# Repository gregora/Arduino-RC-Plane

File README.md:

# Arduino-RC-Plane
An RC airplane, controlled by a custom flight controller based on Arduino Nano.

## CAD

CAD files are available on OnShape [here](https://cad.onshape.com/documents/968e81f1afc8243e275bf7ca/w/acaf7929af669ea720083764/e/5f49399fe13c6903e510c987?renderMode=0&uiState=66e208f6a35c2d67603a374c)

## Controller hardware

The following devices are necessary to recreate the flight controller:
* Arduino Nano microcontroller
* BNO055 Adafruit absolute orientation sensor
* CC1101 radio module

* Flysky radio receiver (or any receiver with iBus)

## Flight modes

The controller enables you to choose from a few different modes of flying. A mode of flying can be chosen by flipping a switch on your radio transmitter on channel 6.

* `Mode 0 - Manual`: Your transmitter outputs are directly linked to the motors.
* `Mode 1 - Take-off`: The aircraft will maintain a 10 degree pitch-up with wings level.
* `Mode 2 - Fly-by-wire` - The aircraft will follow the angular velocity, commanded by the transmitter. For example, a full deflection  of right joystick corresponds to `2*pi rad/s` roll rate.
* `Mode 3 - Automatic` - The aircraft will fly automatically to the desired target position
* `Mode 255 - Recovery`: The aircraft will assume -10 degree pitch down and wings level

## Ground UI

UI for ground control was also written in Python. The UI includes all the necessary information about the flight and enables saving the flight data to a csv file.

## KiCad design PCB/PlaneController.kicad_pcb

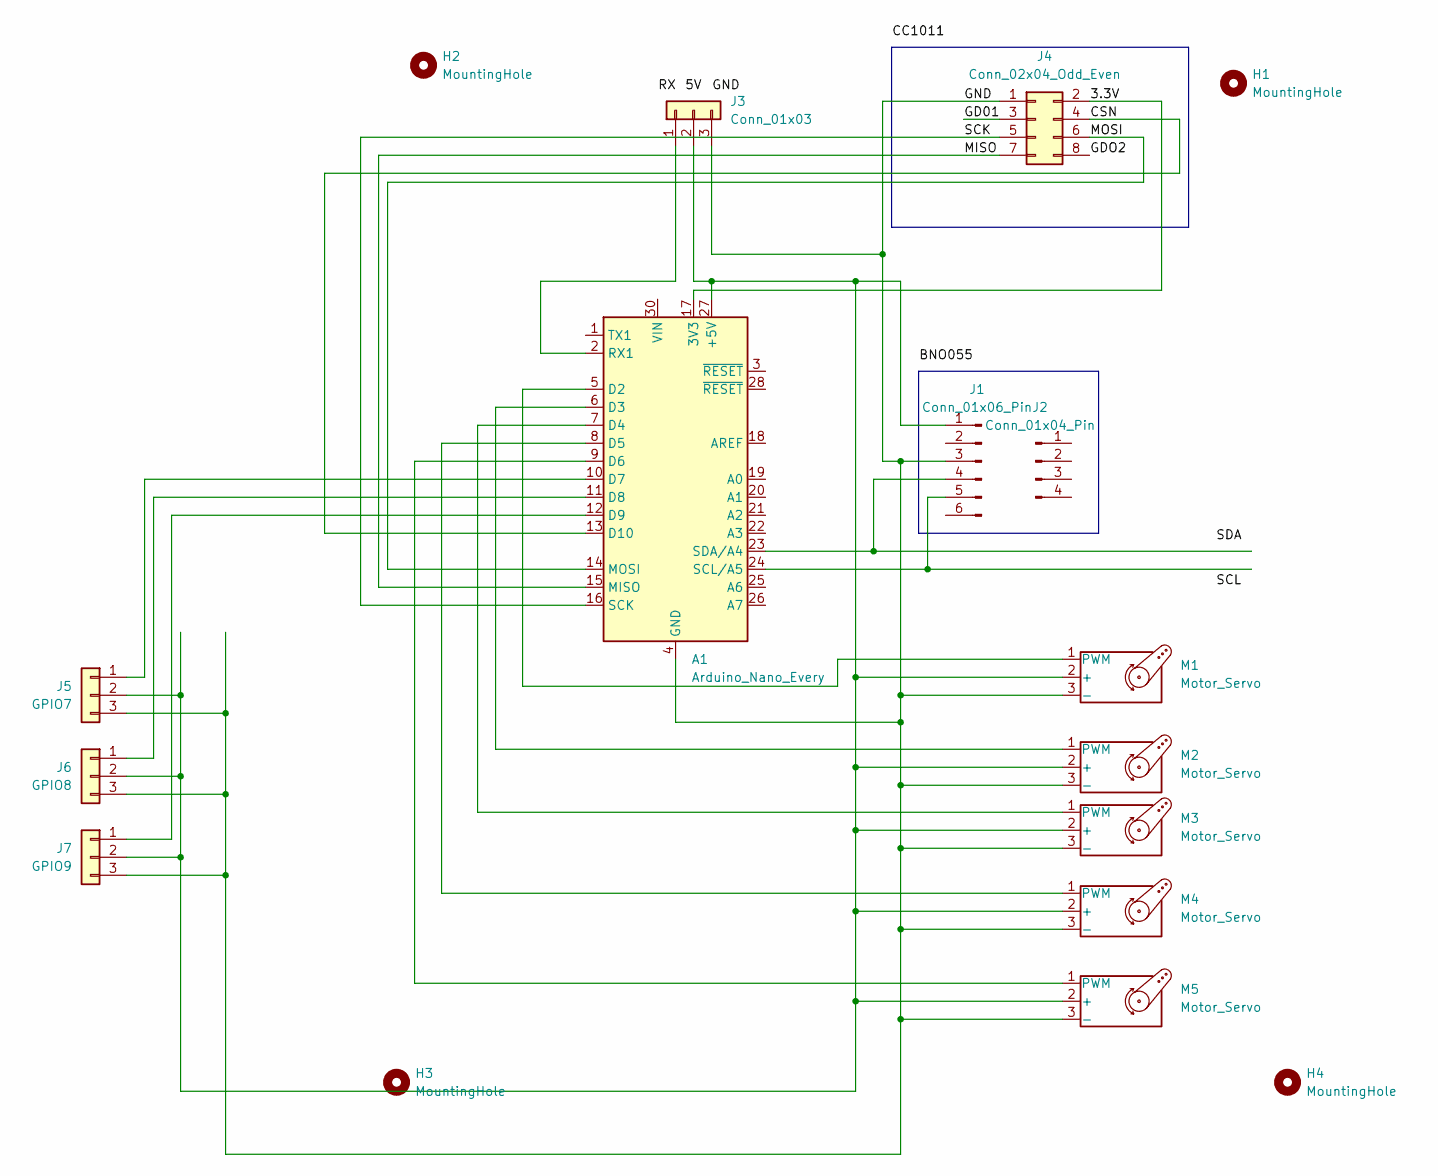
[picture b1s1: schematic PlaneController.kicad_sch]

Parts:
A1: Arduino_Nano_Every; Arduino_Nano
H1, H2, H3, H4: MountingHole; MountingHole_3mm
J1: Conn_01x06_Pin; PinSocket_1x06_P2.54mm_Vertical
J2: Conn_01x04_Pin; PinSocket_1x04_P2.54mm_Vertical
J3: Conn_01x03; PinHeader_1x03_P2.54mm_Vertical
J4: Conn_02x04_Odd_Even; PinSocket_2x04_P2.54mm_Vertical
J5: GPIO7; PinHeader_1x03_P2.54mm_Vertical
J6: GPIO8; PinHeader_1x03_P2.54mm_Vertical
J7: GPIO9; PinHeader_1x03_P2.54mm_Vertical
M1, M2, M3, M4, M5: Motor_Servo; PinHeader_1x03_P2.54mm_Vertical

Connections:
/3.3V: A1.17 (3V3), J4.2
/CSN: A1.13 (D10), J4.4
/GD01: J4.3
/GDO2: J4.8
/GND: A1.4 (GND), A1.29 (GND), J1.3, J3.3, J4.1, J5.3, J6.3, J7.3, M1.3 (-), M2.3 (-), M3.3 (-), M4.3 (-), M5.3 (-)
/MISO: A1.15 (MISO), J4.7
/MOSI: A1.14 (MOSI), J4.6
/SCK: A1.16 (SCK), J4.5
unnamed: A1.27 (+5V), J1.1, J3.2, J5.2, J6.2, J7.2, M1.2 (+), M2.2 (+), M3.2 (+), M4.2 (+), M5.2 (+)
unnamed: A1.5 (D2), M1.1 (PWM)
unnamed: A1.6 (D3), M2.1 (PWM)
unnamed: A1.7 (D4), M3.1 (PWM)
unnamed: A1.8 (D5), M4.1 (PWM)
unnamed: A1.9 (D6), M5.1 (PWM)
unnamed: A1.10 (D7), J5.1
unnamed: A1.11 (D8), J6.1
unnamed: A1.12 (D9), J7.1
unnamed: A1.2 (RX1), J3.1
unnamed: A1.24 (SCL/A5), J1.5
unnamed: A1.23 (SDA/A4), J1.4

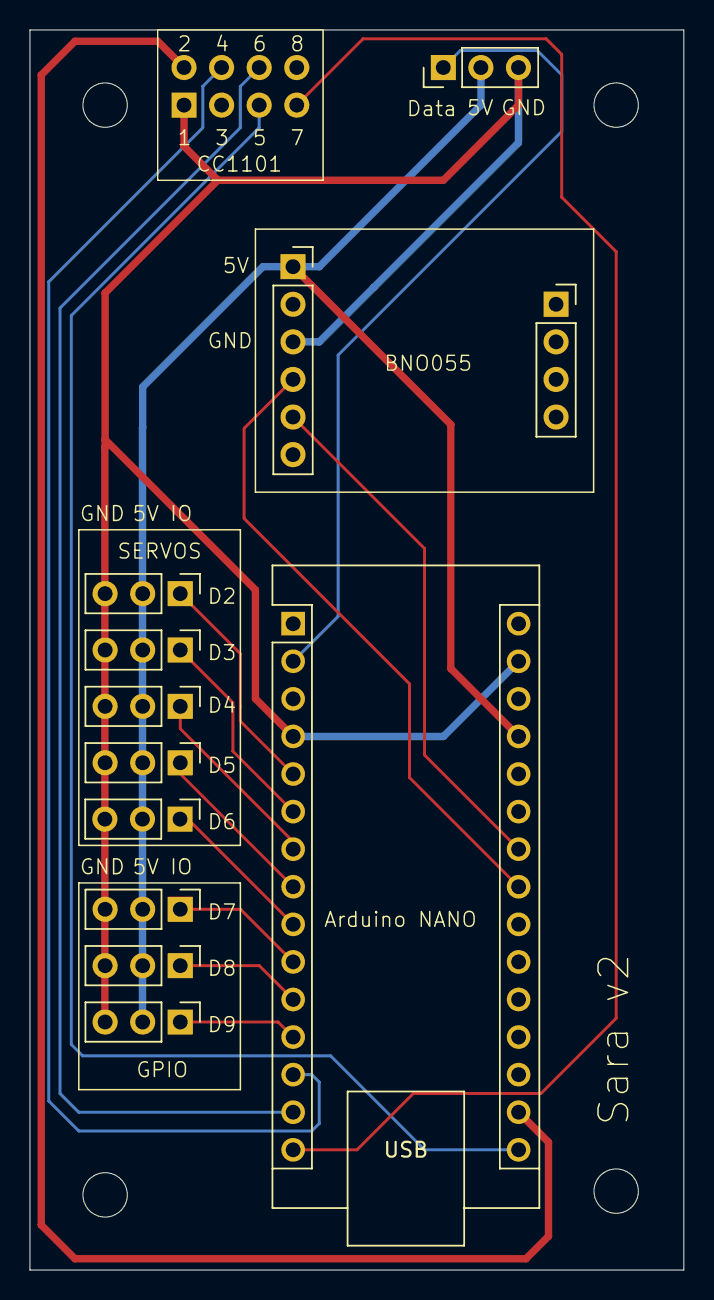
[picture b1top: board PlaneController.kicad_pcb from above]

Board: 2 copper layers, 44.2 x 83.8 mm, 17 parts (1 on the bottom side), 18 nets.

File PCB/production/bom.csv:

Designator,Footprint,Quantity,Value,LCSC Part #
A1,Arduino_Nano,1,Arduino_Nano_Every,
J1,PinSocket_1x06_P2.54mm_Vertical,1,Conn_01x06_Pin,
J2,PinSocket_1x04_P2.54mm_Vertical,1,Conn_01x04_Pin,
J3,PinHeader_1x03_P2.54mm_Vertical,1,Conn_01x03,
J4,PinSocket_2x04_P2.54mm_Vertical,1,Conn_02x04_Odd_Even,
J5,PinHeader_1x03_P2.54mm_Vertical,1,GPIO7,
J6,PinHeader_1x03_P2.54mm_Vertical,1,GPIO8,
J7,PinHeader_1x03_P2.54mm_Vertical,1,GPIO9,
"M1, M2, M3, M4, M5",PinHeader_1x03_P2.54mm_Vertical,5,Motor_Servo,

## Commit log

2024-08-17 Add PCB and CAD files
2024-08-24 Add 5th servo
2024-08-24 Remove PCB locks
2024-08-31 Add RX and TX connections to connect to receiver via iBUS
2024-09-05 Add code for controller v1
2024-09-11 Move files
2024-09-11 Improve PCB footprint
2024-09-25 Start to connect controller to the receiver via iBUS protocol
2024-09-27 Add connection to receiver using 3x1 pin for iBUS, Vcc and GND
2024-09-28 Add PCB traces for CC1101 radio
2024-09-28 Read channels from IBus and send it to ground stations (via I2C)
2024-09-28 Minor changes
2024-09-28 Major PCB fix
2024-09-28 Optimize PCB traces and update code
2024-11-02 Radio is now connected and unnecessary connections are removed from the pcb
2024-11-02 Add 3 more GPIO pins to the main PCB
2024-11-02 Add 3 more GPIO ports
2024-11-03 Add ground station code
2024-11-03 Add turn coordination marker
2024-11-03 Add time
2024-11-03 Add time to controller.ino
2024-11-04 Add status indicator
2024-11-04 Remove backups from git repository
2024-11-04 Add .gitignore
2024-11-04 Add data saving
2024-11-04 Only save if there is anything to save
2024-11-04 Add button for recording
2024-11-04 Minor UI improvements
2024-11-06 Set max telemetry frequency and add debug tools for controller
2024-11-06 Improve ground station packet handling as well
2024-11-07 Read angular velocities from BNO055
2024-11-10 Add fly-by-wire
2024-11-10 Add a simple analyzation tool
2024-11-10 Add a first version of take off mode
2024-11-11 Improve p and d values for take-off mod
2024-11-11 Add Controller Hardware and Flight modes sections to README
2024-11-11 Update description in README
2024-11-11 IMU failure - default to manual mode
2024-11-12 Add recovery mode and add mode to packet
2024-11-12 Fix README
2024-11-12 Implement Fly-by-wire mode
2024-11-15 Bug fix
2024-11-15 Fix bug in pcb
2024-11-15 Set debug to false
2024-11-15 PD tuning
2024-12-05 Partially fix servo jitter bug by removing iBus interrupts
2024-12-05 Add better values for PD controller
2024-12-07 Move BNO055 data collection to getVector instead of getEvent
2024-12-07 Fix jittering by moving servos manually using analogWrite
2025-02-10 Improve P and D controller gains clarity
2025-02-15 Cosmetic changes
2025-02-19 Add magnetometer reading
2025-02-24 Add GPS support on sender and receiver side
2025-02-25 Set GPS speed to 5Hz and remove unnecessary sentances
2025-02-25 Use GPGGA sentances instead of GPRMC
2025-02-25 Increase GPS baudrate
2025-02-25 Ground software fixes and optimizations
2025-02-26 Add minimap display for ground station
2025-02-26 Bug fixes on UI
2025-02-26 Minor UI changes
2025-02-27 Increase precision for attitude
2025-03-12 Read quaternion
2025-03-12 Incorporate quaternions into data downling
2025-03-13 Bug fixes in distance calculations from GPS
2025-04-18 Compute number of fixes per second
2025-07-06 Update Packet class so there are no issues with alignment
2025-07-30 Update ground station
2025-08-01 Somewhat improve radio link range
2025-09-13 Add Automatic mode
2025-10-01 Improve analysis
